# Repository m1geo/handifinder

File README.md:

# Handi-Finder
This repository is a KiCad 5.1 design of the published Handi-Finder DF project. 

The Handi-Finder Project is a radio direction finder, which connectso to an existing radio receiver such as a hand-held radio, and adds some direction finding capabiltiy to it.

The device works by switching between the two wire antennas mounted on H1 and H2 on the PCB. When the two antennas are directly lined towards the source of transmission, the arriving signal is in phase between both antennas. When the Handi-Finder is held non-squarely toward the signal source, the phase difference between the two wire antennas causes the switching frequency (here, approximately 1 kHz) to be audiable with loudness proportional to phase difference.

There are many resources online for this project, with some links here:
- [May 1993 QST Article by Bob K8DTS](https://www.ve5nn.ca/images/FoxHunt/handi-finder.pdf)
- [The HANDI-Finder](https://www.handi-finder.com/)

The [outputs](https://github.com/m1geo/handifinder/tree/main/Outputs) folder contains the Gerber files which can be zipped up and sent for manufacture at your chosen board-house.

## 3D View

## Schematic

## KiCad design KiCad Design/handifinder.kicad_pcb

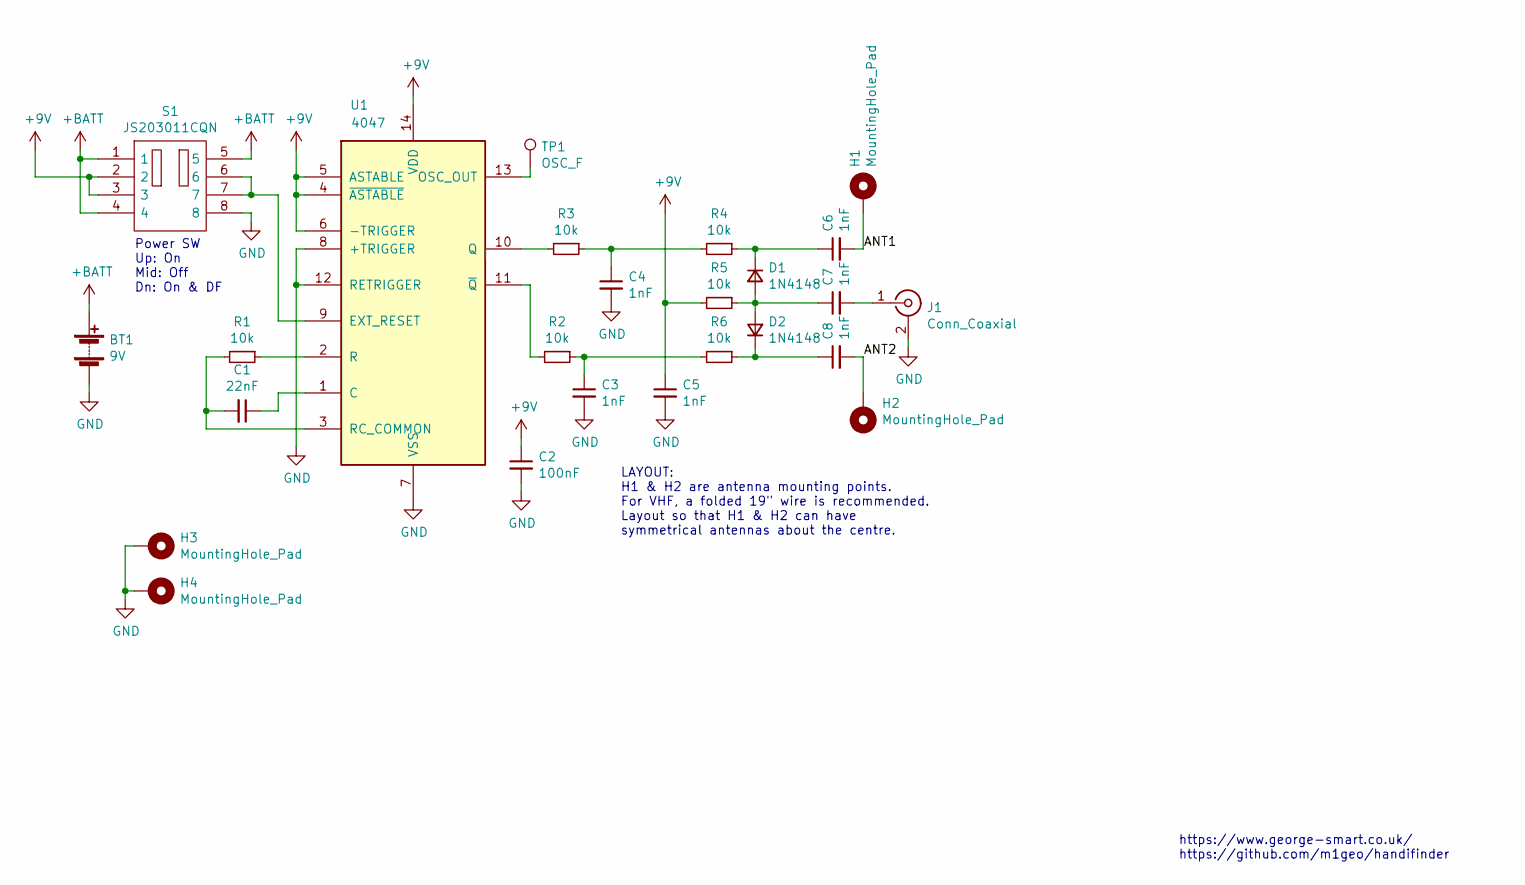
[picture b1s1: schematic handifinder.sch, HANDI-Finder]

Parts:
BT1: 9V; BH9VPC
C1: 22nF; C_0805_2012Metric_Pad1.18x1.45mm_HandSolder
C2: 100nF; C_0805_2012Metric_Pad1.18x1.45mm_HandSolder
C3, C4, C5, C6, C7, C8: 1nF; C_0805_2012Metric_Pad1.18x1.45mm_HandSolder
D1, D2: 1N4148; D_SOD-123
H1, H2, H3, H4: MountingHole_Pad; MountingHole_3.2mm_M3_Pad_Via
J1: Conn_Coaxial; SMA_Amphenol_132134_Vertical
R1, R2, R3, R4, R5, R6: 10k; R_0805_2012Metric_Pad1.20x1.40mm_HandSolder
S1: JS203011CQN; JS-DP3T; Manufacturer_Part_Number JS203011CQN; Mouser Part Number 611-JS203011CQN
TP1: OSC_F; TestPoint_Pad_D2.5mm
U1: 4047; SOIC-14_3.9x8.7mm_P1.27mm

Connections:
+9V: C2.1, C5.1, R5.2, S1.2, S1.3, U1.4 (~ASTABLE), U1.5 (ASTABLE), U1.6 (-TRIGGER), U1.14 (VDD)
+BATT: BT1.1 (+), S1.1, S1.4, S1.5
/ANT1: C6.2, H1.1
/ANT2: C8.2, H2.1
GND: BT1.2 (-), C2.2, C3.2, C4.2, C5.2, H3.1, H4.1, J1.2 (Ext), S1.8, U1.7 (VSS), U1.8 (+TRIGGER), U1.12 (RETRIGGER)
unnamed: C1.1, U1.1 (C)
unnamed: C1.2, R1.2, U1.3 (RC_COMMON)
unnamed: C3.1, R2.1, R6.2
unnamed: C4.1, R3.1, R4.2
unnamed: C6.1, D1.1 (K), R4.1
unnamed: C7.1, D1.2 (A), D2.2 (A), R5.1
unnamed: C7.2, J1.1 (In)
unnamed: C8.1, D2.1 (K), R6.1
unnamed: R1.1, U1.2 (R)
unnamed: R2.2, U1.11 (~Q)
unnamed: R3.2, U1.10 (Q)
unnamed: S1.6, S1.7, U1.9 (EXT_RESET)
unnamed: TP1.1, U1.13 (OSC_OUT)

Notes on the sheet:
https://www.george-smart.co.uk/ https://github.com/m1geo/handifinder
LAYOUT: H1 & H2 are antenna mounting points. For VHF, a folded 19" wire is recommended. Layout so that H1 & H2 can have symmetrical antennas about the centre.
Power SW Up: On Mid: Off Dn: On & DF

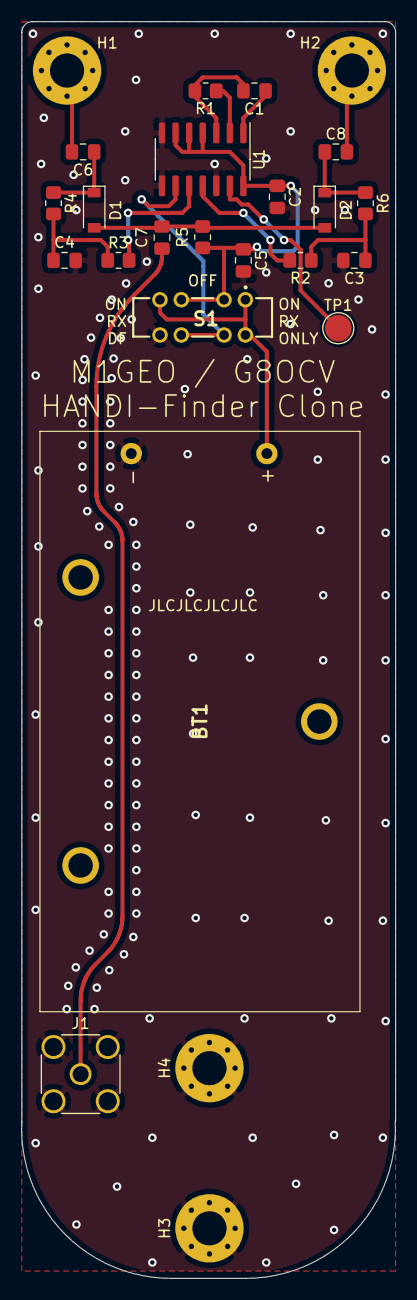
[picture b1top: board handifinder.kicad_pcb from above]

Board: 2 copper layers, 35.0 x 117.7 mm, 25 parts (0 on the bottom side), 18 nets.

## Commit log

2022-05-18 Handi-Finder Files Commit
2022-05-18 Fixed readme link error
